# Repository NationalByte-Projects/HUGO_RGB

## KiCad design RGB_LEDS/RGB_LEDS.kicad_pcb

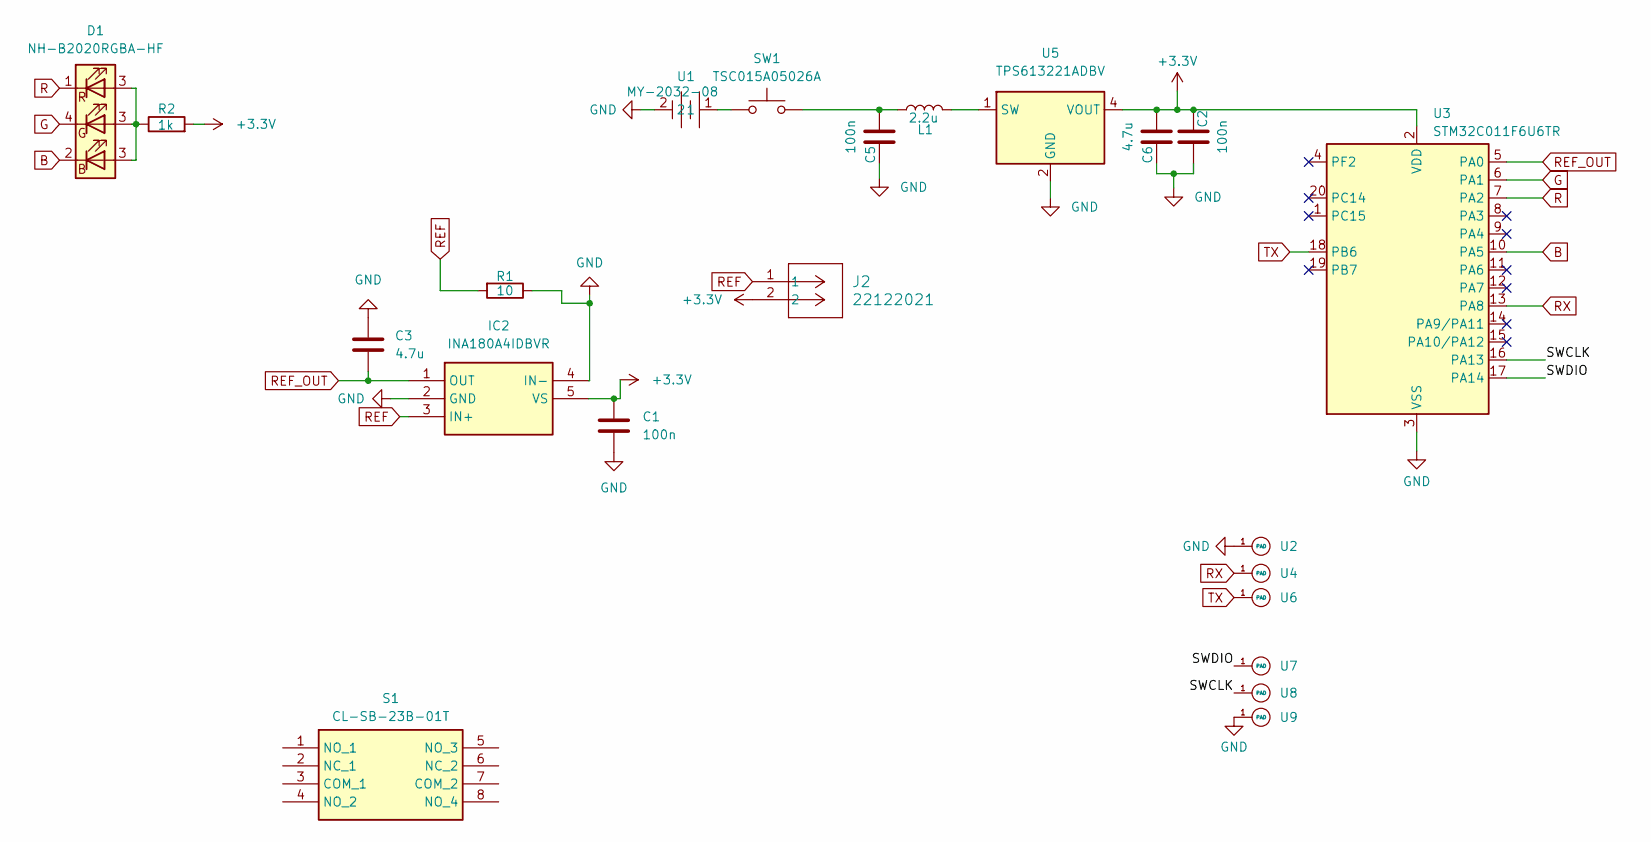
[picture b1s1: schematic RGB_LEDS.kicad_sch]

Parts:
C1: 100n; C_0603_1608Metric
C2, C5: 100n; C_0402_1005Metric
C3: 4.7u; C_0603_1608Metric
C6: 4.7u; C_0402_1005Metric
D1: NH-B2020RGBA-HF; LED-ARRAY-SMD_4P-L2.1-W2.1-TL_NH-B2020RGBA
IC2: INA180A4IDBVR; SOT95P280X145-5N; Manufacturer_Part_Number INA180A4IDBVR; Mouser Part Number 595-INA180A4IDBVR
J2: 22122021; CONN_A-4094-02A_MOL
L1: 2.2u; L_0805_2012Metric
R1: 10; R_0603_1608Metric
R2: 1k; R_0603_1608Metric
S1: CL-SB-23B-01T; CLSB23B01T; Manufacturer_Part_Number CL-SB-23B-01T; Mouser Part Number 229-CL-SB-23B-01T
SW1: TSC015A05026A; SW-SMD_4P-L4.5-W4.5-P3.00-LS6.8
U1: MY-2032-08; BAT-SMD_MY-2032-08
U2, U4, U6, U7, U8, U9: TestPoint_Pad_1.0x1.0mm
U3: STM32C011F6U6TR; ST_UFQFPN-20_3x3mm_P0.5mm
U5: TPS613221ADBV; SOT-23-5

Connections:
+3.3V: C1.1, C2.2, C6.1, IC2.5 (VS), J2.2, R2.2, U3.2 (VDD), U5.4 (VOUT)
/SWCLK: U3.16 (PA13), U8.1 (PAD)
/SWDIO: U3.17 (PA14), U7.1 (PAD)
B: D1.2 (BK), U3.10 (PA5)
G: D1.4 (GK), U3.6 (PA1)
GND: C1.2, C2.1, C3.2, C5.2, C6.2, IC2.2 (GND), IC2.4 (IN-), R1.1, U1.2, U2.1 (PAD), U3.3 (VSS), U5.2 (GND), U9.1 (PAD)
unnamed: C5.1, L1.1, SW1.2
unnamed: D1.3, R2.1
unnamed: SW1.1, U1.1
unnamed: L1.2, U5.1 (SW)
R: D1.1 (RK), U3.7 (PA2)
REF: IC2.3 (IN+), J2.1, R1.2
REF_OUT: C3.1, IC2.1 (OUT), U3.5 (PA0)
RX: U3.13 (PA8), U4.1 (PAD)
TX: U3.18 (PB6), U6.1 (PAD)

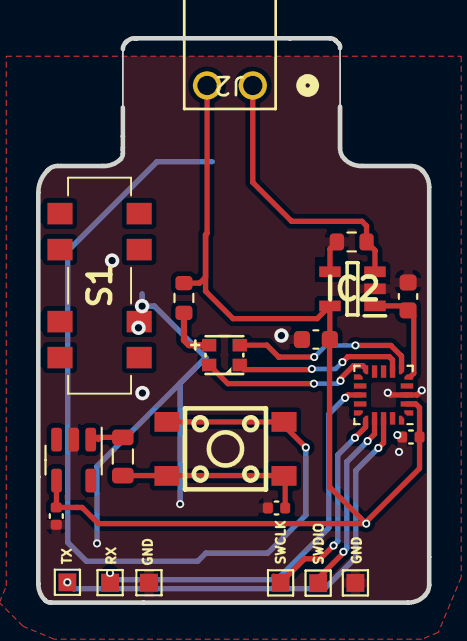
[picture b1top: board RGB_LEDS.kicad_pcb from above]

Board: 2 copper layers, 21.7 x 31.4 mm, 22 parts (1 on the bottom side), 15 nets.

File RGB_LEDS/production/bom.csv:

Designator,Footprint,Quantity,Value,LCSC Part #
C1,0603,1,100n,
"C2, C5",0402,2,100n,
C3,0603,1,4.7u,
C6,0402,1,4.7u,
D1,LED-ARRAY-SMD_4P-L2.1-W2.1-TL_NH-B2020RGBA,1,NH-B2020RGBA-HF,
IC2,SOT95P280X145-5N,1,INA180A4IDBVR,
J2,CONN_A-4094-02A_MOL,1,22122021,
L1,0805,1,2.2u,
R1,0603,1,10,
R2,0603,1,1k,
SW1,SW-SMD_4P-L4.5-W4.5-P3.00-LS6.8,1,SW_Push,
U1,BAT-SMD_MY-2032-08,1,MY-2032-08,
"U2, U4, U6, U7, U8, U9",TestPoint_Pad_1.0x1.0mm,6,~,
U3,ST_UFQFPN-20_3x3mm_P0.5mm,1,STM32C011F6U6TR,
U5,SOT-23-5,1,TPS613221ADBV,

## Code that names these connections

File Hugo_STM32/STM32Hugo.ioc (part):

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Mcu.Name=STM32C011F(4-6)Ux
Mcu.Package=UFQFPN20
Mcu.UserName=STM32C011F4Ux
PA0.Mode=IN0
PA0.Signal=ADC1_IN0
PA1.Signal=S_TIM1_CH2
PA13.Mode=Serial_Wire
PA13.Signal=DEBUG_SWDIO
PA14-BOOT0.Mode=Serial_Wire
PA14-BOOT0.Signal=DEBUG_SWCLK
PA2.Signal=S_TIM1_CH3
PA5.Signal=S_TIM1_CH1
PA8.Mode=Asynchronous
PA8.Signal=USART1_RX
PB6.Mode=Asynchronous
PB6.Signal=USART1_TX
RCC.HSE_VALUE=8000000
RCC.SYSCLKFreq_VALUE=12000000
board=custom

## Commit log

2024-11-11 Cheaper, using uC now, instead of full analog
2024-12-02 Code and PCB
2025-03-22 Placa con stm32, selector de voltaje se necesita quitar una vez que se decida por un valor
2025-05-24 sent to manufacture
2025-05-24 Changed to correct chip
2025-05-24 initial test
2025-05-24 reads Current Correctly
2025-05-25 Turns led on
2025-08-10 final version, longer connector, 3.3 only
2025-08-26 Added selector
2025-08-26 added 3d model locally
2025-08-26 local 3d
2025-09-01 selector
